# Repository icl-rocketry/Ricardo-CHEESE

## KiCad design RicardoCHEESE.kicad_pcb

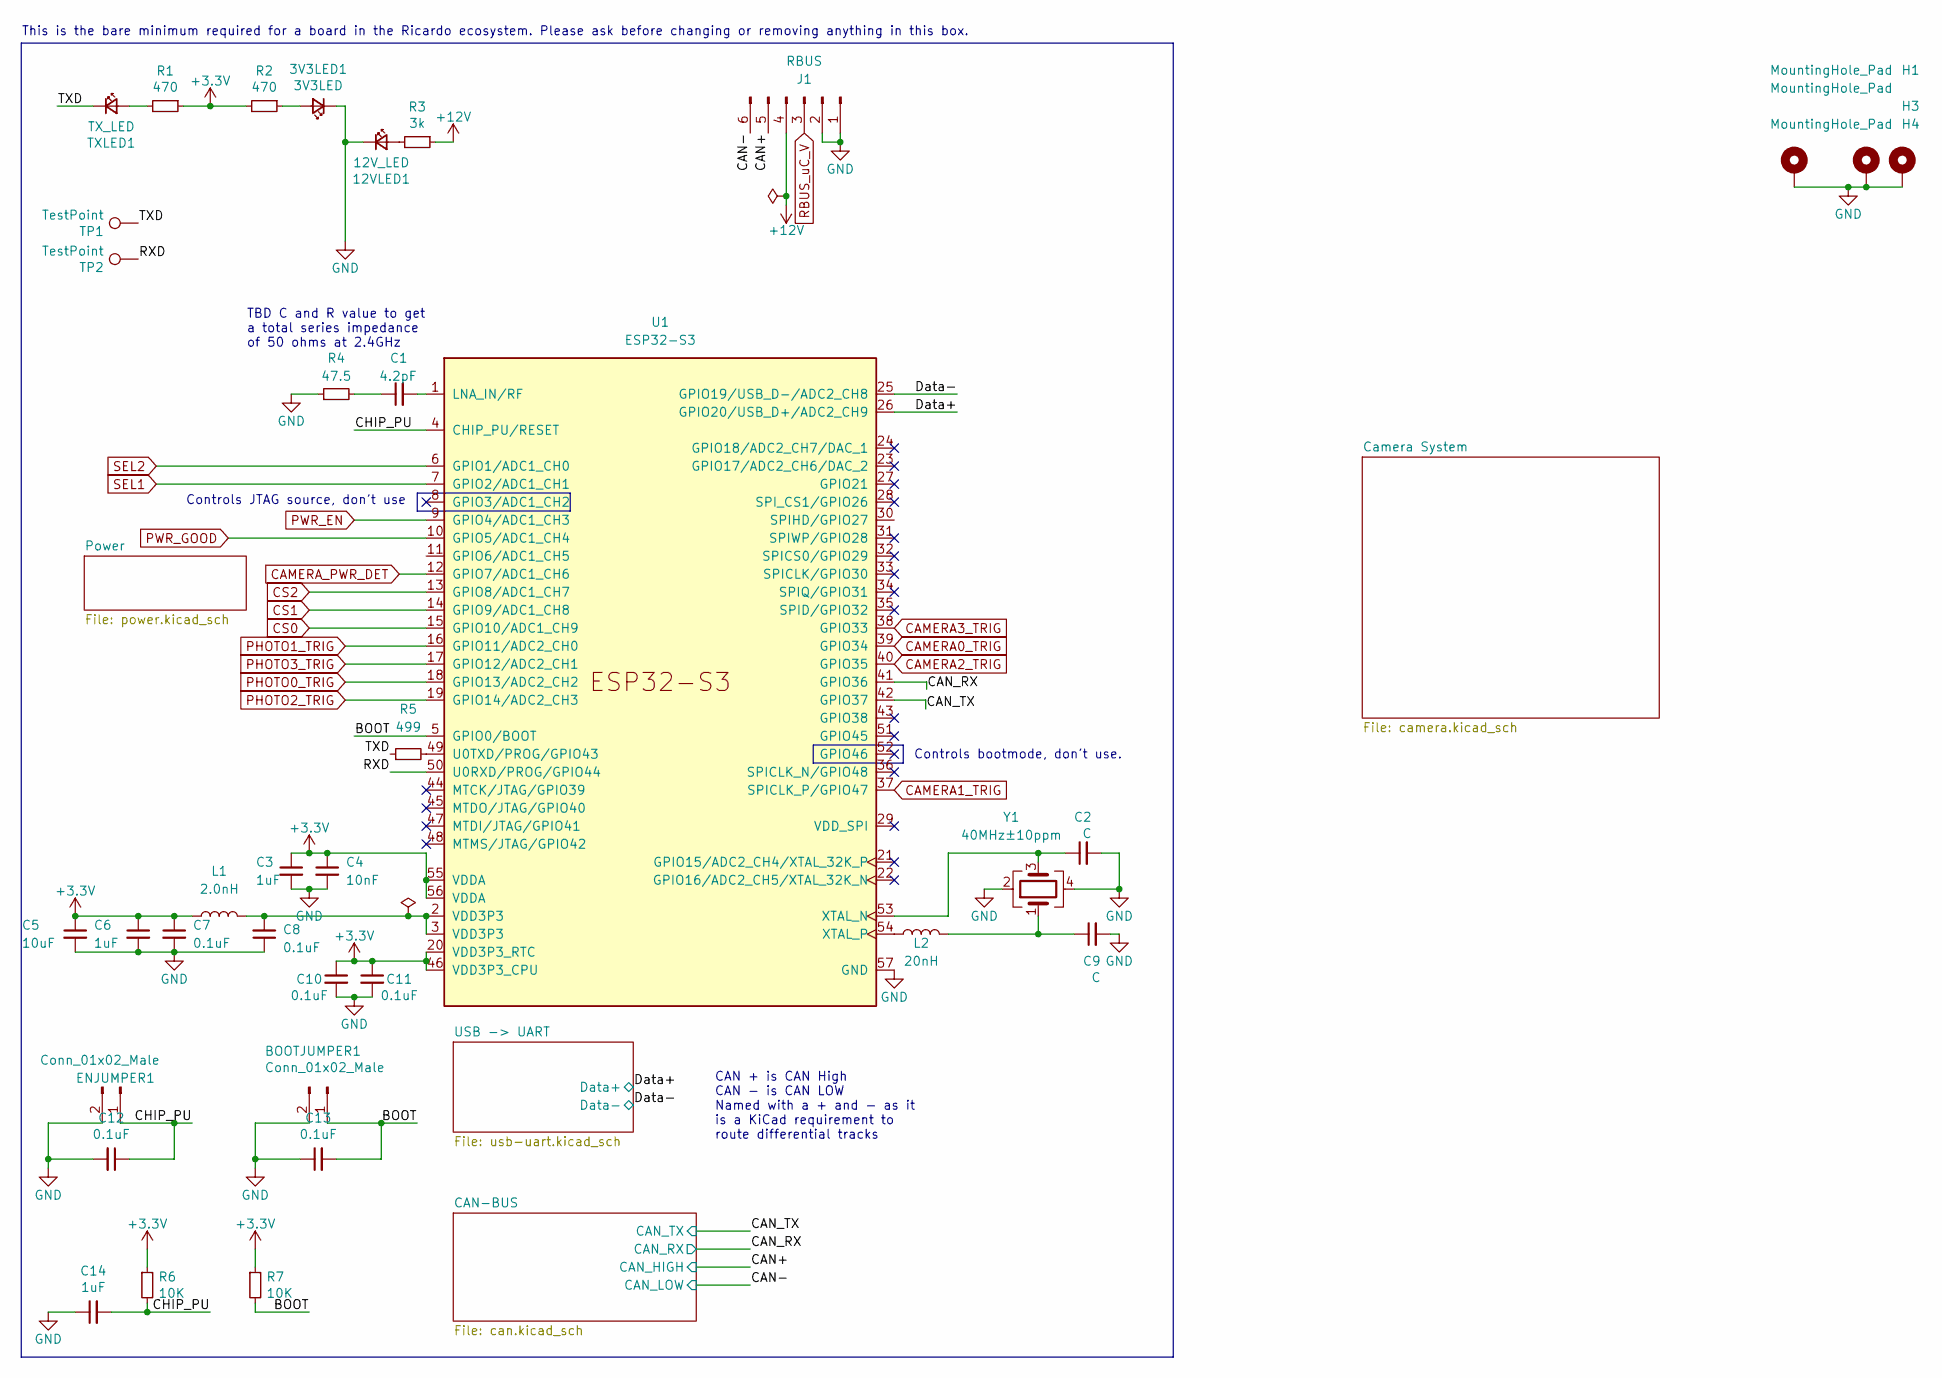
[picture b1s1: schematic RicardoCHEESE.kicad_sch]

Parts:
3V3LED1: 3V3LED; LED_0402_1005Metric
12VLED1: 12V_LED; LED_0603_1608Metric
BOOTJUMPER1: Conn_01x02_Male; PinHeader_1x02_P2.54mm_Vertical
C1: 4.2pF; C_0402_1005Metric
C2, C9: C; C_0402_1005Metric
C3, C6, C14: 1uF; C_0402_1005Metric
C4: 10nF; C_0402_1005Metric
C5: 10uF; C_0402_1005Metric
C7, C8, C10, C11, C12, C13: 0.1uF; C_0402_1005Metric
ENJUMPER1: Conn_01x02_Male; PinHeader_1x02_P2.54mm_Vertical
H1, H3, H4: MountingHole_Pad; MountingHole_3.2mm_M3_DIN965_Pad
J1: RBUS; Molex_Mini-Fit_Jr_5566-06A_2x03_P4.20mm_Vertical
L1: 2.0nH; L_0402_1005Metric
L2: 20nH; L_0402_1005Metric
R1, R2: 470; R_0402_1005Metric
R3: 3k; R_0402_1005Metric
R4: 47.5; R_0402_1005Metric
R5: 499; R_0402_1005Metric
R6, R7: 10K; R_0402_1005Metric
TP1, TP2: TestPoint; TestPoint_Pad_D1.0mm
TXLED1: TX_LED; R_0402_1005Metric
U1: ESP32-S3; QFN40P700X700X90-57N
Y1: 40MHz±10ppm; Crystal_SMD_2016-4Pin_2.0x1.6mm

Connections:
+3.3V: C3.1, C4.1, C5.1, C6.1, C7.1, C10.1, C11.1, L1.1, R1.1, R2.2, R6.1, R7.1, U1.20 (VDD3P3_RTC), U1.46 (VDD3P3_CPU), U1.55 (VDDA), U1.56 (VDDA); also elsewhere on the board
+12V: J1.4, R3.1
/BOOT: BOOTJUMPER1.1, C13.2, R7.2, U1.5 (GPIO0/BOOT)
/CAN+: J1.5; also elsewhere on the board
/CAN-: J1.6; also elsewhere on the board
/CAN_RX: U1.41 (GPIO36); also elsewhere on the board
/CAN_TX: U1.42 (GPIO37); also elsewhere on the board
/CHIP_PU: C12.1, C14.2, ENJUMPER1.1, R6.2, U1.4 (CHIP_PU/RESET)
/Data+: U1.26 (GPIO20/USB_D+/ADC2_CH9); also elsewhere on the board
/Data-: U1.25 (GPIO19/USB_D-/ADC2_CH8); also elsewhere on the board
/RXD: TP2.1, U1.50 (U0RXD/PROG/GPIO44)
/TXD: R5.1, TP1.1, TXLED1.1 (K)
CAMERA0_TRIG: U1.39 (GPIO34); also elsewhere on the board
CAMERA1_TRIG: U1.37 (SPICLK_P/GPIO47); also elsewhere on the board
CAMERA2_TRIG: U1.40 (GPIO35); also elsewhere on the board
CAMERA3_TRIG: U1.38 (GPIO33); also elsewhere on the board
CAMERA_PWR_DET: U1.12 (GPIO7/ADC1_CH6); also elsewhere on the board
CS0: U1.15 (GPIO10/ADC1_CH9); also elsewhere on the board
CS1: U1.14 (GPIO9/ADC1_CH8); also elsewhere on the board
CS2: U1.13 (GPIO8/ADC1_CH7); also elsewhere on the board
unnamed: 3V3LED1.2 (A), R2.1
unnamed: 12VLED1.2 (A), R3.2
unnamed: C1.1, R4.2
unnamed: C8.2, L1.2, U1.2 (VDD3P3), U1.3 (VDD3P3)
unnamed: C9.1, L2.2, Y1.1
unnamed: R1.2, TXLED1.2 (A)
unnamed: C1.2, U1.1 (LNA_IN/RF)
unnamed: R5.2, U1.49 (U0TXD/PROG/GPIO43)
unnamed: C2.1, U1.53 (XTAL_N), Y1.3
unnamed: L2.1, U1.54 (XTAL_P)
PHOTO0_TRIG: U1.18 (GPIO13/ADC2_CH2); also elsewhere on the board
PHOTO1_TRIG: U1.16 (GPIO11/ADC2_CH0); also elsewhere on the board
PHOTO2_TRIG: U1.19 (GPIO14/ADC2_CH3); also elsewhere on the board
PHOTO3_TRIG: U1.17 (GPIO12/ADC2_CH1); also elsewhere on the board
PWR_EN: U1.9 (GPIO4/ADC1_CH3); also elsewhere on the board
PWR_GOOD: U1.10 (GPIO5/ADC1_CH4); also elsewhere on the board
RBUS_uC_V: J1.3; also elsewhere on the board
SEL1: U1.7 (GPIO2/ADC1_CH1); also elsewhere on the board
SEL2: U1.6 (GPIO1/ADC1_CH0); also elsewhere on the board

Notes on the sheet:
Controls bootmode, don't use.
This is the bare minimum required for a board in the Ricardo ecosystem. Please ask before changing or removing anything in this box.
TBD C and R value to get a total series impedance of 50 ohms at 2.4GHz
CAN + is CAN High CAN - is CAN LOW Named with a + and - as it is a KiCad requirement to route differential tracks
Controls JTAG source, don't use

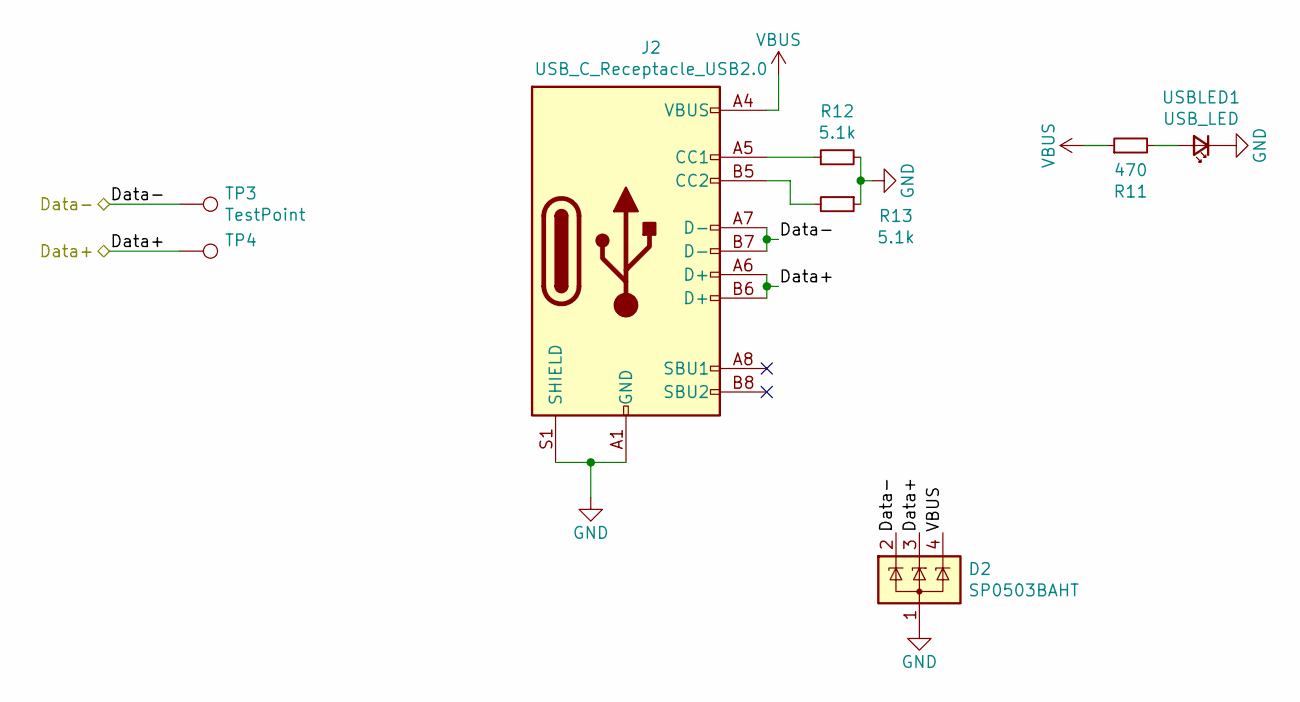
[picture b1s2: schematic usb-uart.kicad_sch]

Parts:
D2: SP0503BAHT; SOT-143
J2: USB_C_Receptacle_USB2.0; USB_C_Receptacle_Palconn_UTC16-G
R11: 470; R_0402_1005Metric
R12, R13: 5.1k; R_0402_1005Metric
TP3, TP4: TestPoint; TestPoint_Pad_D1.0mm
USBLED1: USB_LED; R_0402_1005Metric

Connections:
/Data+: D2.3 (K), J2.A6 (D+), J2.B6 (D+), TP4.1; also elsewhere on the board
/Data-: D2.2 (K), J2.A7 (D-), J2.B7 (D-), TP3.1; also elsewhere on the board
unnamed: J2.A5 (CC1), R12.1
unnamed: J2.B5 (CC2), R13.2
unnamed: R11.2, USBLED1.2 (A)
VBUS: D2.4 (K), J2.A4 (VBUS), J2.A9 (VBUS), J2.B4 (VBUS), J2.B9 (VBUS), R11.1; also elsewhere on the board

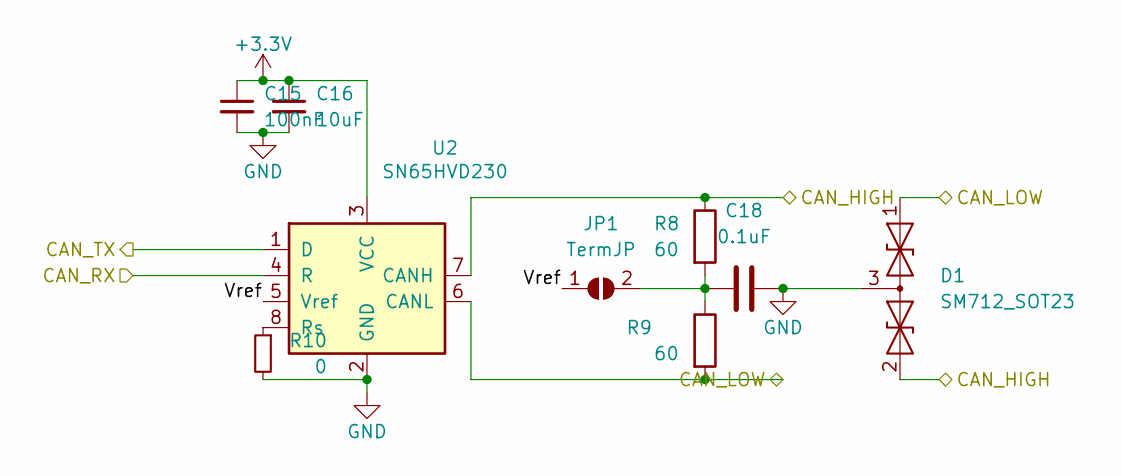
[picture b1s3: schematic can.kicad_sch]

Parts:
C15: 100nF; C_0402_1005Metric
C16: 10uF; C_0603_1608Metric
C18: 0.1uF; C_0402_1005Metric
D1: SM712_SOT23; SOT-23
JP1: TermJP; SolderJumper-2_P1.3mm_Open_RoundedPad1.0x1.5mm
R8, R9: 60; R_0402_1005Metric
R10: 0; R_0603_1608Metric
U2: SN65HVD230; SOIC-8_3.9x4.9mm_P1.27mm

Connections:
+3.3V: C15.1, C16.1, U2.3 (VCC); also elsewhere on the board
/CAN+: D1.2 (A2), R8.1, U2.7 (CANH); also elsewhere on the board
/CAN-: D1.1 (A1), R9.2, U2.6 (CANL); also elsewhere on the board
/CAN-BUS/Vref: JP1.1 (A), U2.5 (Vref)
/CAN_RX: U2.4 (R); also elsewhere on the board
/CAN_TX: U2.1 (D); also elsewhere on the board
unnamed: C18.1, JP1.2 (B), R8.2, R9.1
unnamed: R10.1, U2.8 (Rs)

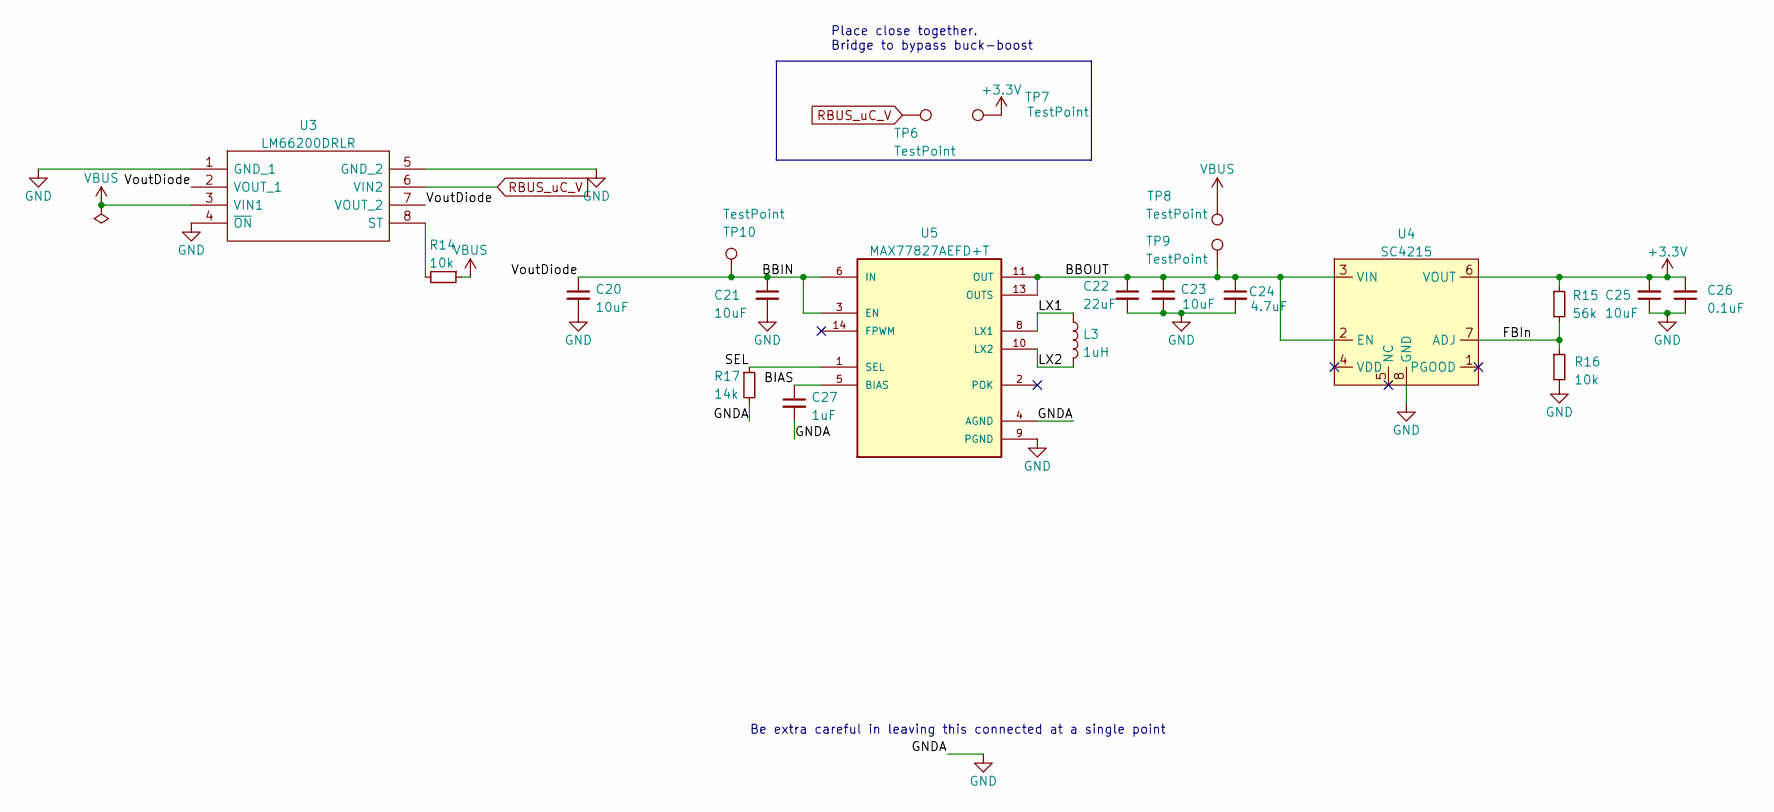
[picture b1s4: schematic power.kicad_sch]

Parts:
C20, C21, C25: 10uF; C_0603_1608Metric
C22: 22uF; C_0603_1608Metric
C23: 10uF; C_0402_1005Metric
C24: 4.7uF; C_0402_1005Metric
C26: 0.1uF; C_0402_1005Metric
C27: 1uF; C_0402_1005Metric
L3: 1uH; L_0805_2012Metric
R14, R16: 10k; R_0402_1005Metric
R15: 56k; R_0402_1005Metric
R17: 14k; R_0402_1005Metric
TP6, TP7, TP8, TP9, TP10: TestPoint; TestPoint_Pad_D1.5mm
U3: LM66200DRLR; SOTFL50P160X60-8N; Manufacturer_Part_Number LM66200DRLR; Mouser Part Number 595-LM66200DRLR
U4: SC4215; SOIC127P599X175-8N
U5: MAX77827AEFD+T; CONV_MAX77827AEFD+T; PARTREV B

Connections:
+3.3V: C25.2, C26.2, R15.1, TP7.1, U4.6 (VOUT); also elsewhere on the board
/Power/BBIN: C20.1, C21.1, TP10.1, U3.2 (VOUT_1), U3.7 (VOUT_2), U5.3 (EN), U5.6 (IN)
/Power/BBOUT: C22.1, C23.1, C24.1, TP9.1, U4.2 (EN), U4.3 (VIN), U5.11 (OUT), U5.13 (OUTS)
/Power/BIAS: C27.1, U5.5 (BIAS)
/Power/FBIn: R15.2, R16.1, U4.7 (ADJ)
/Power/LX1: L3.1, U5.8 (LX1)
/Power/LX2: L3.2, U5.10 (LX2)
/Power/SEL: R17.1, U5.1 (SEL)
unnamed: R14.2, U3.8 (ST)
RBUS_uC_V: TP6.1, U3.6 (VIN2); also elsewhere on the board
VBUS: R14.1, TP8.1, U3.3 (VIN1); also elsewhere on the board

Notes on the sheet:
Place close together. Bridge to bypass buck-boost
Be extra careful in leaving this connected at a single point

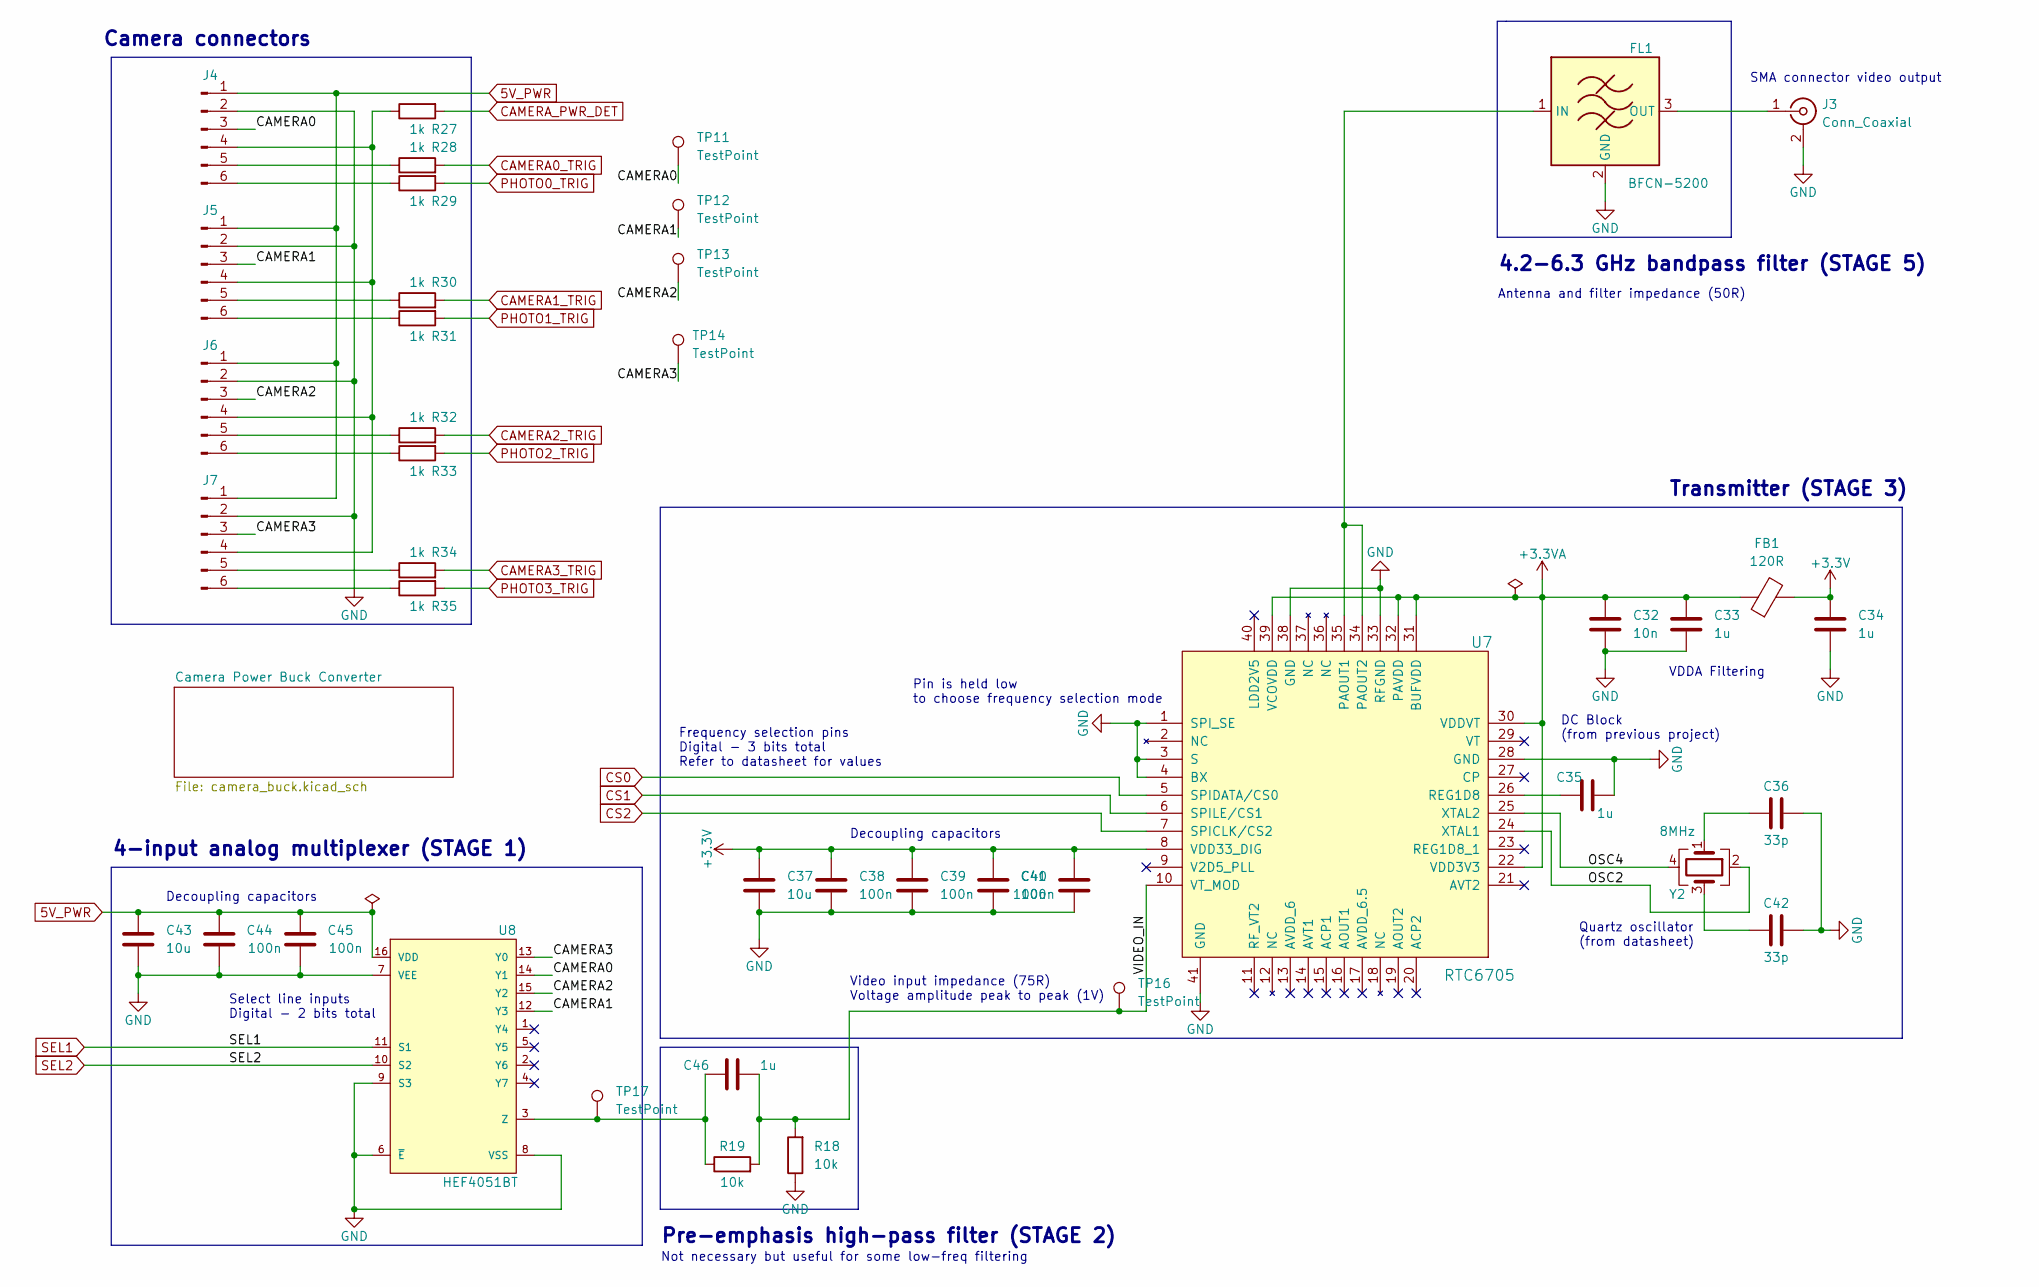
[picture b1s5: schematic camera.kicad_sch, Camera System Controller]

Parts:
C32: 10n; C_0402_1005Metric
C33, C34, C35: 1u; C_0402_1005Metric
C36, C42: 33p; C_0402_1005Metric
C37, C43: 10u; C_0603_1608Metric
C38, C39, C40, C41, C44, C45: 100n; C_0402_1005Metric
C46: 1u; C_0603_1608Metric
FB1: 120R; L_0402_1005Metric
FL1: BFCN-5200; Filter_Mini-Circuits_FV1206-4
J3: Conn_Coaxial; SMA_Molex_73251-1153_EdgeMount_Horizontal
J4, J5, J6, J7: Conn_01x06_Pin; JST_PH_S6B-PH-K_1x06_P2.00mm_Horizontal
R18, R19: 10k; R_0402_1005Metric
R27, R28, R29, R30, R31, R32, R33, R34, R35: 1k; R_0402_1005Metric
TP11, TP12, TP13, TP14, TP16, TP17: TestPoint; TestPoint_Pad_D1.0mm
U7: RTC6705
U8: HEF4051BT; SOIC127P600X175-16N; Voltage - Supply, Singl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 3 V ~{} 15 V; mouser part number 771-HEF4051BTD-T; digikey description 1 Circuit IC Switch 8:1 155 Ohm 16-SO
Y2: 8MHz; Crystal_SMD_0603-4Pin_6.0x3.5mm

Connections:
5V_PWR: C43.1, C44.2, C45.2, J4.1, J5.1, J6.1, J7.1, U8.16 (VDD); also elsewhere on the board
+3.3V: C34.1, C37.1, C38.1, C39.1, C40.1, C41.1, FB1.2, U7.8 (VDD33_DIG); also elsewhere on the board
+3.3VA: C32.1, C33.1, FB1.1, U7.22 (VDD3V3), U7.30 (VDDVT), U7.31 (BUFVDD), U7.32 (PAVDD), U7.39 (VCOVDD)
/Camera System/CAMERA0: J4.3, TP11.1, U8.14 (Y1)
/Camera System/CAMERA1: J5.3, TP12.1, U8.12 (Y3)
/Camera System/CAMERA2: J6.3, TP13.1, U8.15 (Y2)
/Camera System/CAMERA3: J7.3, TP14.1, U8.13 (Y0)
/Camera System/OSC2: U7.24 (XTAL1), Y2.2
/Camera System/OSC4: U7.25 (XTAL2), Y2.4
/Camera System/VIDEO_IN: C46.2, R18.2, R19.2, TP16.1, U7.10 (VT_MOD)
CAMERA0_TRIG: R28.2; also elsewhere on the board
CAMERA1_TRIG: R30.2; also elsewhere on the board
CAMERA2_TRIG: R32.2; also elsewhere on the board
CAMERA3_TRIG: R34.2; also elsewhere on the board
CAMERA_PWR_DET: R27.2; also elsewhere on the board
CS0: U7.5 (SPIDATA/CS0); also elsewhere on the board
CS1: U7.6 (SPILE/CS1); also elsewhere on the board
CS2: U7.7 (SPICLK/CS2); also elsewhere on the board
unnamed: C36.1, Y2.1
unnamed: C42.1, Y2.3
unnamed: FL1.1 (IN), U7.34 (PAOUT2), U7.35 (PAOUT1)
unnamed: FL1.3 (OUT), J3.1 (In)
unnamed: J4.4, J5.4, J6.4, J7.4, R27.1
unnamed: J4.5, R28.1
unnamed: J4.6, R29.1
unnamed: J5.5, R30.1
unnamed: J5.6, R31.1
unnamed: J6.5, R32.1
unnamed: J6.6, R33.1
unnamed: J7.5, R34.1
unnamed: C35.1, U7.26 (REG1D8)
unnamed: C46.1, R19.1, TP17.1, U8.3 (Z)
PHOTO0_TRIG: R29.2; also elsewhere on the board
PHOTO1_TRIG: R31.2; also elsewhere on the board
PHOTO2_TRIG: R33.2; also elsewhere on the board
PHOTO3_TRIG: R35.2; also elsewhere on the board
SEL1: U8.11 (S1); also elsewhere on the board
SEL2: U8.10 (S2); also elsewhere on the board

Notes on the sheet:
4.2-6.3 GHz bandpass filter (STAGE 5)
Decoupling capacitors
Not necessary but useful for some low-freq filtering
Antenna and filter impedance (50R)
Select line inputs Digital - 2 bits total
Frequency selection pins Digital - 3 bits total Refer to datasheet for values
Video input impedance (75R) Voltage amplitude peak to peak (1V)
Pin is held low to choose frequency selection mode
Quartz oscillator (from datasheet)
Transmitter (STAGE 3)
Camera connectors
VDDA Filtering
DC Block (from previous project)
SMA connector video output
4-input analog multiplexer (STAGE 1)
Pre-emphasis high-pass filter (STAGE 2)

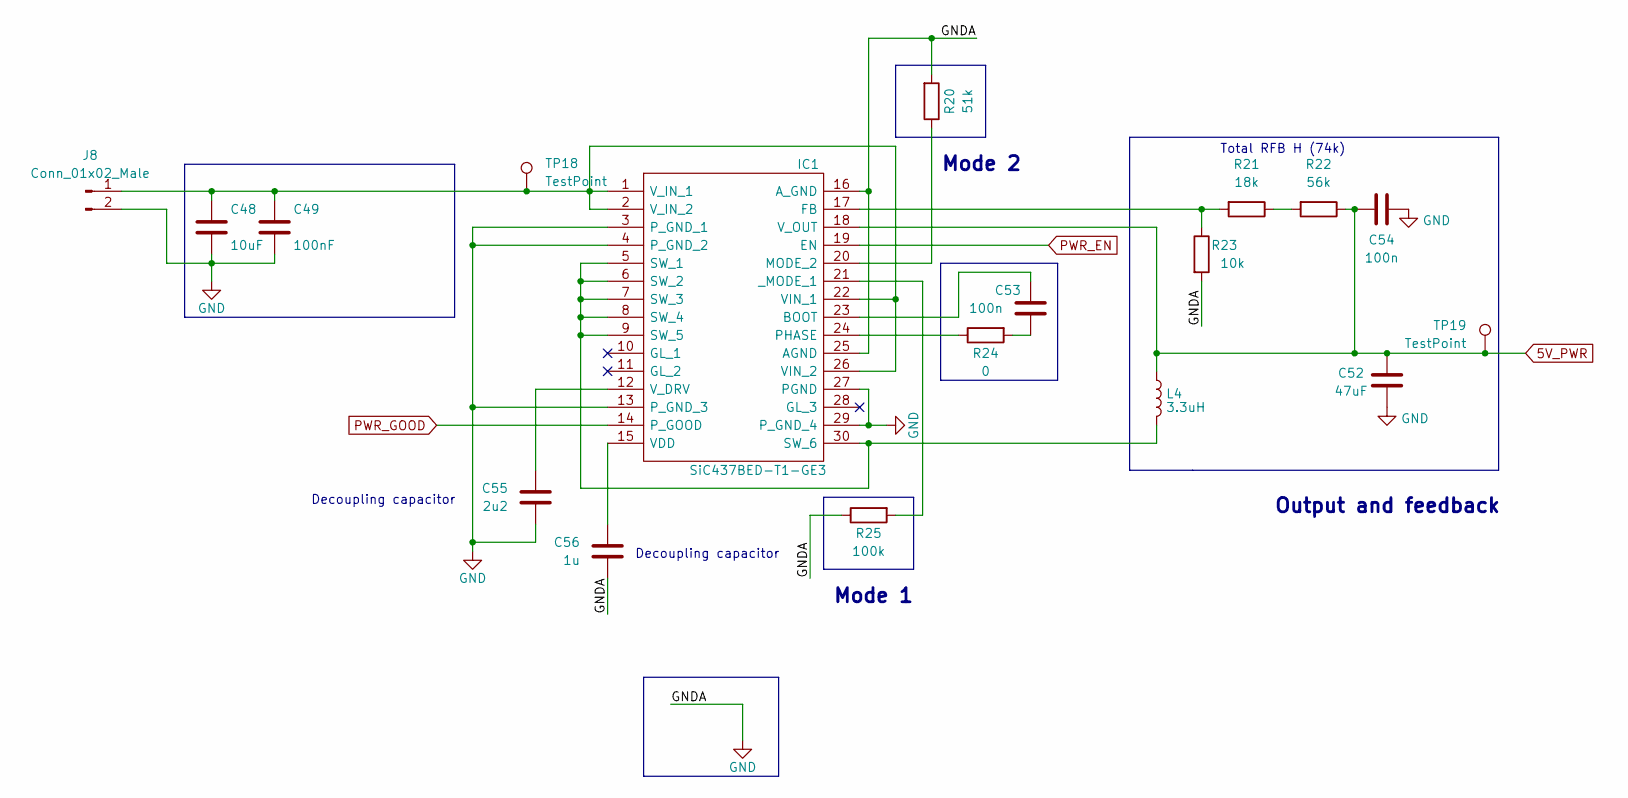
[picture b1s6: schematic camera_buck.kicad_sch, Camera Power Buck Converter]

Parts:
C48: 10uF; C_0603_1608Metric
C49: 100nF; C_0402_1005Metric
C52: 47uF; C_1206_3216Metric
C53, C54: 100n; C_0402_1005Metric
C55: 2u2; C_0402_1005Metric
C56: 1u; C_0402_1005Metric
IC1: SiC437BED-T1-GE3; SiC437BEDT1GE3; Manufacturer_Part_Number SiC437BED-T1-GE3; Mouser Part Number 78-SIC437BED-T1-GE3
J8: Conn_01x02_Male; AMASS_XT30PW-M_1x02_P2.50mm_Horizontal
L4: 3.3uH; INDPM110100X540N
R20: 51k; R_0402_1005Metric
R21: 18k; R_0402_1005Metric
R22: 56k; R_0402_1005Metric
R23: 10k; R_0402_1005Metric
R24: 0; R_0603_1608Metric
R25: 100k; R_0402_1005Metric
TP18, TP19: TestPoint; TestPoint_Pad_D1.0mm

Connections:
5V_PWR: C52.2, C54.1, IC1.18 (V_OUT), L4.1, R22.1, TP19.1; also elsewhere on the board
unnamed: C53.2, R24.2
unnamed: C53.1, IC1.23 (BOOT)
unnamed: IC1.17 (FB), R21.2, R23.1
unnamed: IC1.20 (MODE_2), R20.1
unnamed: IC1.24 (PHASE), R24.1
unnamed: IC1.5 (SW_1), IC1.6 (SW_2), IC1.7 (SW_3), IC1.8 (SW_4), IC1.9 (SW_5), IC1.30 (SW_6), L4.2
unnamed: C56.2, IC1.15 (VDD)
unnamed: C48.1, C49.1, IC1.1 (V_IN_1), IC1.2 (V_IN_2), IC1.22 (VIN_1), IC1.26 (VIN_2), J8.1, TP18.1
unnamed: C55.2, IC1.12 (V_DRV)
unnamed: IC1.21 (_MODE_1), R25.2
unnamed: R21.1, R22.2
PWR_EN: IC1.19 (EN); also elsewhere on the board
PWR_GOOD: IC1.14 (P_GOOD); also elsewhere on the board

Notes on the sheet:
Total RFB H (74k)
Decoupling capacitor
Mode 2
Output and feedback
Mode 1

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
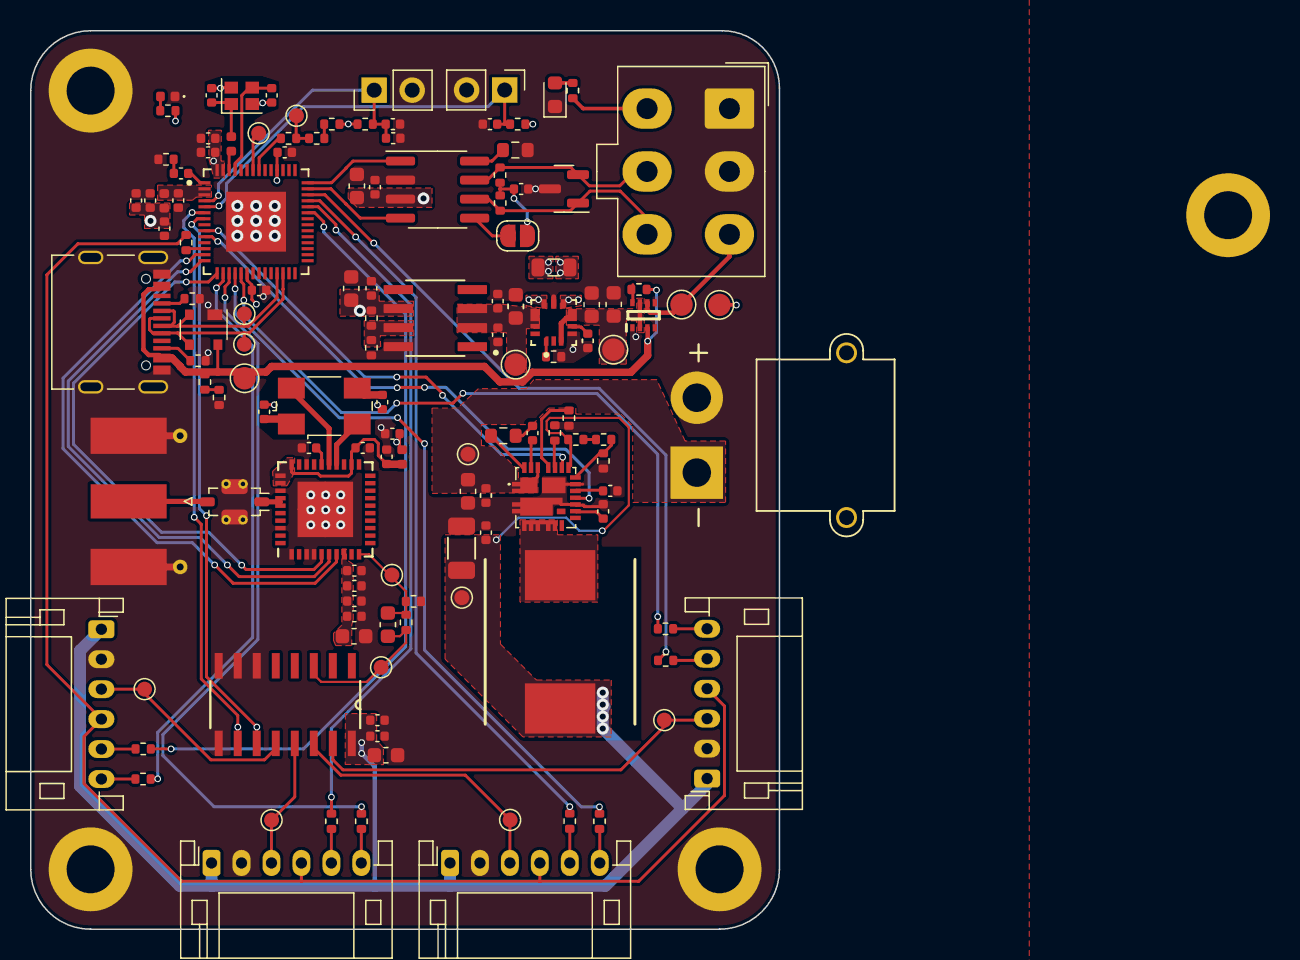
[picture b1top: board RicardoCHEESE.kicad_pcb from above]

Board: 4 copper layers, 50.0 x 60.0 mm, 134 parts (0 on the bottom side), 90 nets.

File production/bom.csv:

Designator,Footprint,Quantity,Value,LCSC Part #
3V3LED1,0402,1,BLUE_LED,
"BOOTJUMPER1, ENJUMPER1",PinHeader_1x02_P2.54mm_Vertical,2,Conn_01x02_Male,
C1,0402,1,4.2pF,
"C10, C11, C12, C13, C26, C7, C8",0402,7,0.1uF,
"C14, C27, C3, C6",0402,4,1uF,
"C15, C49",0402,2,100nF,
"C16, C23, C25, C5",0402,4,10uF,
C18,0402,1,47nF,
"C2, C9",0402,2,C,
"C20, C21",0603,2,10uF,
C22,0603,1,22uF,
C24,0402,1,4.7uF,
C32,0402,1,10n,
"C33, C34, C35, C46, C56",0402,5,1u,
"C36, C42",0402,2,24p,
C37,0402,1,10u,
"C38, C39, C40, C41, C44, C45, C53, C54",0402,8,100n,
C4,0402,1,10nF,
C43,0603,1,10u,
"C48, C52",1206,2,47uF,
C55,0402,1,2u2,
D1,SOT-23,1,SM712_SOT23,
D2,SOT-143,1,SP0503BAHT,
FB1,0402,1,120R,
FL1,Filter_Mini-Circuits_FV1206-4,1,BFCN-5200,
"H1, H3, H4",MountingHole_3.2mm_M3_DIN965_Pad,3,MountingHole_Pad,
IC1,SiC437BEDT1GE3,1,SiC437BED-T1-GE3,
J1,Molex_Mini-Fit_Jr_5566-06A_2x03_P4.20mm_Vertical,1,RBUS,
J2,USB_C_Receptacle_Palconn_UTC16-G,1,USB_C_Receptacle_USB2.0,
J3,SMA_Molex_73251-1153_EdgeMount_Horizontal,1,Conn_Coaxial,
"J4, J5, J6, J7",JST_PH_S6B-PH-K_1x06_P2.00mm_Horizontal,4,Conn_01x06_Pin,
J8,AMASS_XT30PW-M_1x02_P2.50mm_Horizontal,1,Conn_01x02_Male,
JP1,SolderJumper-2_P1.3mm_Open_RoundedPad1.0x1.5mm,1,TermJP,
L1,0402,1,2.0nH,
L2,0402,1,20nH,
L3,0805,1,1uH,
L4,INDPM110100X540N,1,3.3uH,
"R1, R2",0402,2,470,
R10,0603,1,0,
R11,0402,1,3000,
"R12, R13",0402,2,5.1k,
"R14, R16, R18, R19, R23, R3, R6, R7",0402,8,10k,
"R15, R22",0402,2,56k,
R17,0402,1,14k,
"R20, R26",0402,2,51k,
R21,0402,1,18k,
R24,0402,1,2.2,
R25,0402,1,100k,
"R27, R28, R29, R30, R31, R32, R33, R34, R35",0402,9,1k,
R4,0402,1,47.5,
R5,0402,1,499,
"R8, R9",0603,2,60,
"TP1, TP11, TP12, TP13, TP14, TP16, TP17, TP2, TP3, TP4",TestPoint_Pad_D1.0mm,10,TestPoint,
"TP10, TP6, TP7, TP8, TP9",TestPoint_Pad_D1.5mm,5,TestPoint,
TXLED1,0402,1,GREEN_LED,
U1,QFN40P700X700X90-57N,1,ESP32-S3,
U2,SOIC-8_3.9x4.9mm_P1.27mm,1,SN65HVD230,
U3,SOTFL50P160X60-8N,1,LM66200DRLR,
U4,SOIC127P599X175-9N,1,SC4215,
U5,CONV_MAX77827AEFD+T,1,MAX77827AEFD+T,
U7,RTC6705,1,RTC6705,
U8,SOIC127P600X175-16N,1,HEF4051BT,
USBLED1,0402,1,USB_LED,
Y1,Crystal_SMD_2016-4Pin_2.0x1.6mm,1,40MHz±10ppm,
Y2,Crystal_SMD_0603-4Pin_6.0x3.5mm,1,8MHz,

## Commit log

2023-05-27 File names and ERC
2023-05-27 Add photo triggers
2023-05-27 Add datasheets and sample project
2023-05-27 Fixed libraries and footprints
2023-05-27 User saved
2023-05-30 Placing footprints
2023-05-31 Board layout
2023-06-06 Some routing
2023-06-10 Camera buck changes, c and r footprints, other
2023-06-21 Footprinting and board outline
2023-06-27 CHEESE routing finished V1
2023-06-27 Finished routing
2023-08-20 radio side needs reviewing
2023-08-29 post andrei review
2023-09-04 fixed some stuff
2023-09-05 ordering
2024-09-21 Conforming folder structure, added firmware
2024-09-22 submodules
